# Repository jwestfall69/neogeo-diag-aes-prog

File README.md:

# neogeo-diag-aes-prog

## Overview
This is a custom NeoGeo AES Prog board that is used in conjunction with the [NeoGeo Diag Bios](https://github.com/jwestfall69/neogeo-diag-bios) that allows for testing the P ROM address and data buses between the motherboard and the cart slot.  Its meant to help trouble shoot getting a blue screen or if your game cart boots then crashes after a while (possible faulty P ROM bank switching).

It works by using an SRAM chip instead of a ROM for the program rom on the PROG board.  Doing this allows the diag bios to run tests on it similar to that of work ram to find issues.

Its not possible to test all lines related to the program rom, so there are 2 leds at the top of the board.  These 2 LEDs (ROMOE, PORTADDR) should be lit up when the P ROM Bus tests are running in the diag bios.

## PCB Manufacturing
PCB should be 1.6mm thickness.  With these boards likely being inserted and removed numerous times its suggested you use ENIG surface finishing and gold fingers w/45 degree chamfering.

I've been using [jlcpcb](https://jlcpcb.com/) for PCB manufacturing.  Just watch out that by default they will add an order number to the silk screen unless you tell them not to.

## BOM
| Quantity | Description | Part Number | Digikey | Notes |
|:--------:|:------------|-------------|---------|-------|
| 1        | SRAM 8Mbit 44 pin TSOP II | AS6C8016-55ZIN | [1450-1041-ND](https://www.digikey.com/en/products/detail/alliance-memory-inc/AS6C8016-55ZIN/4234600) | |
| 1        | 74LS04 pin 14 SOIC | SN74LS04DR | [296-14875-2-ND](https://www.digikey.com/en/products/detail/texas-instruments/SN74LS04DR/562927) | |
| 1        | 74LS08 pin 14 SOIC | SN74LS08DR | [296-14879-2-ND](https://www.digikey.com/en/products/detail/texas-instruments/SN74LS08DR/562906) | |
| 1        | 74LS11 pin 14 SOIC | SN74LS11DR | [296-28984-2-ND](https://www.digikey.com/en/products/detail/texas-instruments/SN74LS11DR/1571760) | |
| 5        | 100nf / 0.1uf Ceramic Capacitor 0805 Size | CL21B104KBCNNNC | [1276-1003-2-ND](https://www.digikey.com/en/products/detail/samsung-electro-mechanics/CL21B104KBCNNNC/3886661) | Any 100nf 0805 is fine |
| 2        | 1K Ohm resistor 0805 Size | ERJ-6GEYJ102V | [P1.0KACT-ND](https://www.digikey.com/en/products/detail/panasonic-electronic-components/ERJ-6GEYJ102V/83014) | Any 1K 0805 resistor is fine |
| 2        | Green LED 0805 12mcd | LTST-C171GKT | [160-1423-2-ND](https://www.digikey.com/en/products/detail/liteon/LTST-C171GKT/386793) | Other 0805 size LEDs should be fine |

## Assembly
The SRAM has a really fine pin pitch, so take your time.  Other then that nothing special.

## Usage
The prog board should be used along with a valid CHA board.  Ideally you probably want a full diag cart where the CHA board has the M1 diag rom and this PROG board.  The cart should be inserted into the slot and then boot the board with the diag bios. Goto the main menu screen.

Pick: ```P ROM BUS TESTS (CUSTOM CART)```

Since this is an AES you won't be able to change the slot number, so either press A+C to start the tests or D to go back to the main menu.

The tests will run continually until D is pressed or an issue is detected.  While the tests are running you should expect the 2 LEDs on the PROG board to be lit up.

If you attempt to run the P rom bus tests without the diag PROG board you will get a ```P2 UNWRITABLE (LOWER)``` error.

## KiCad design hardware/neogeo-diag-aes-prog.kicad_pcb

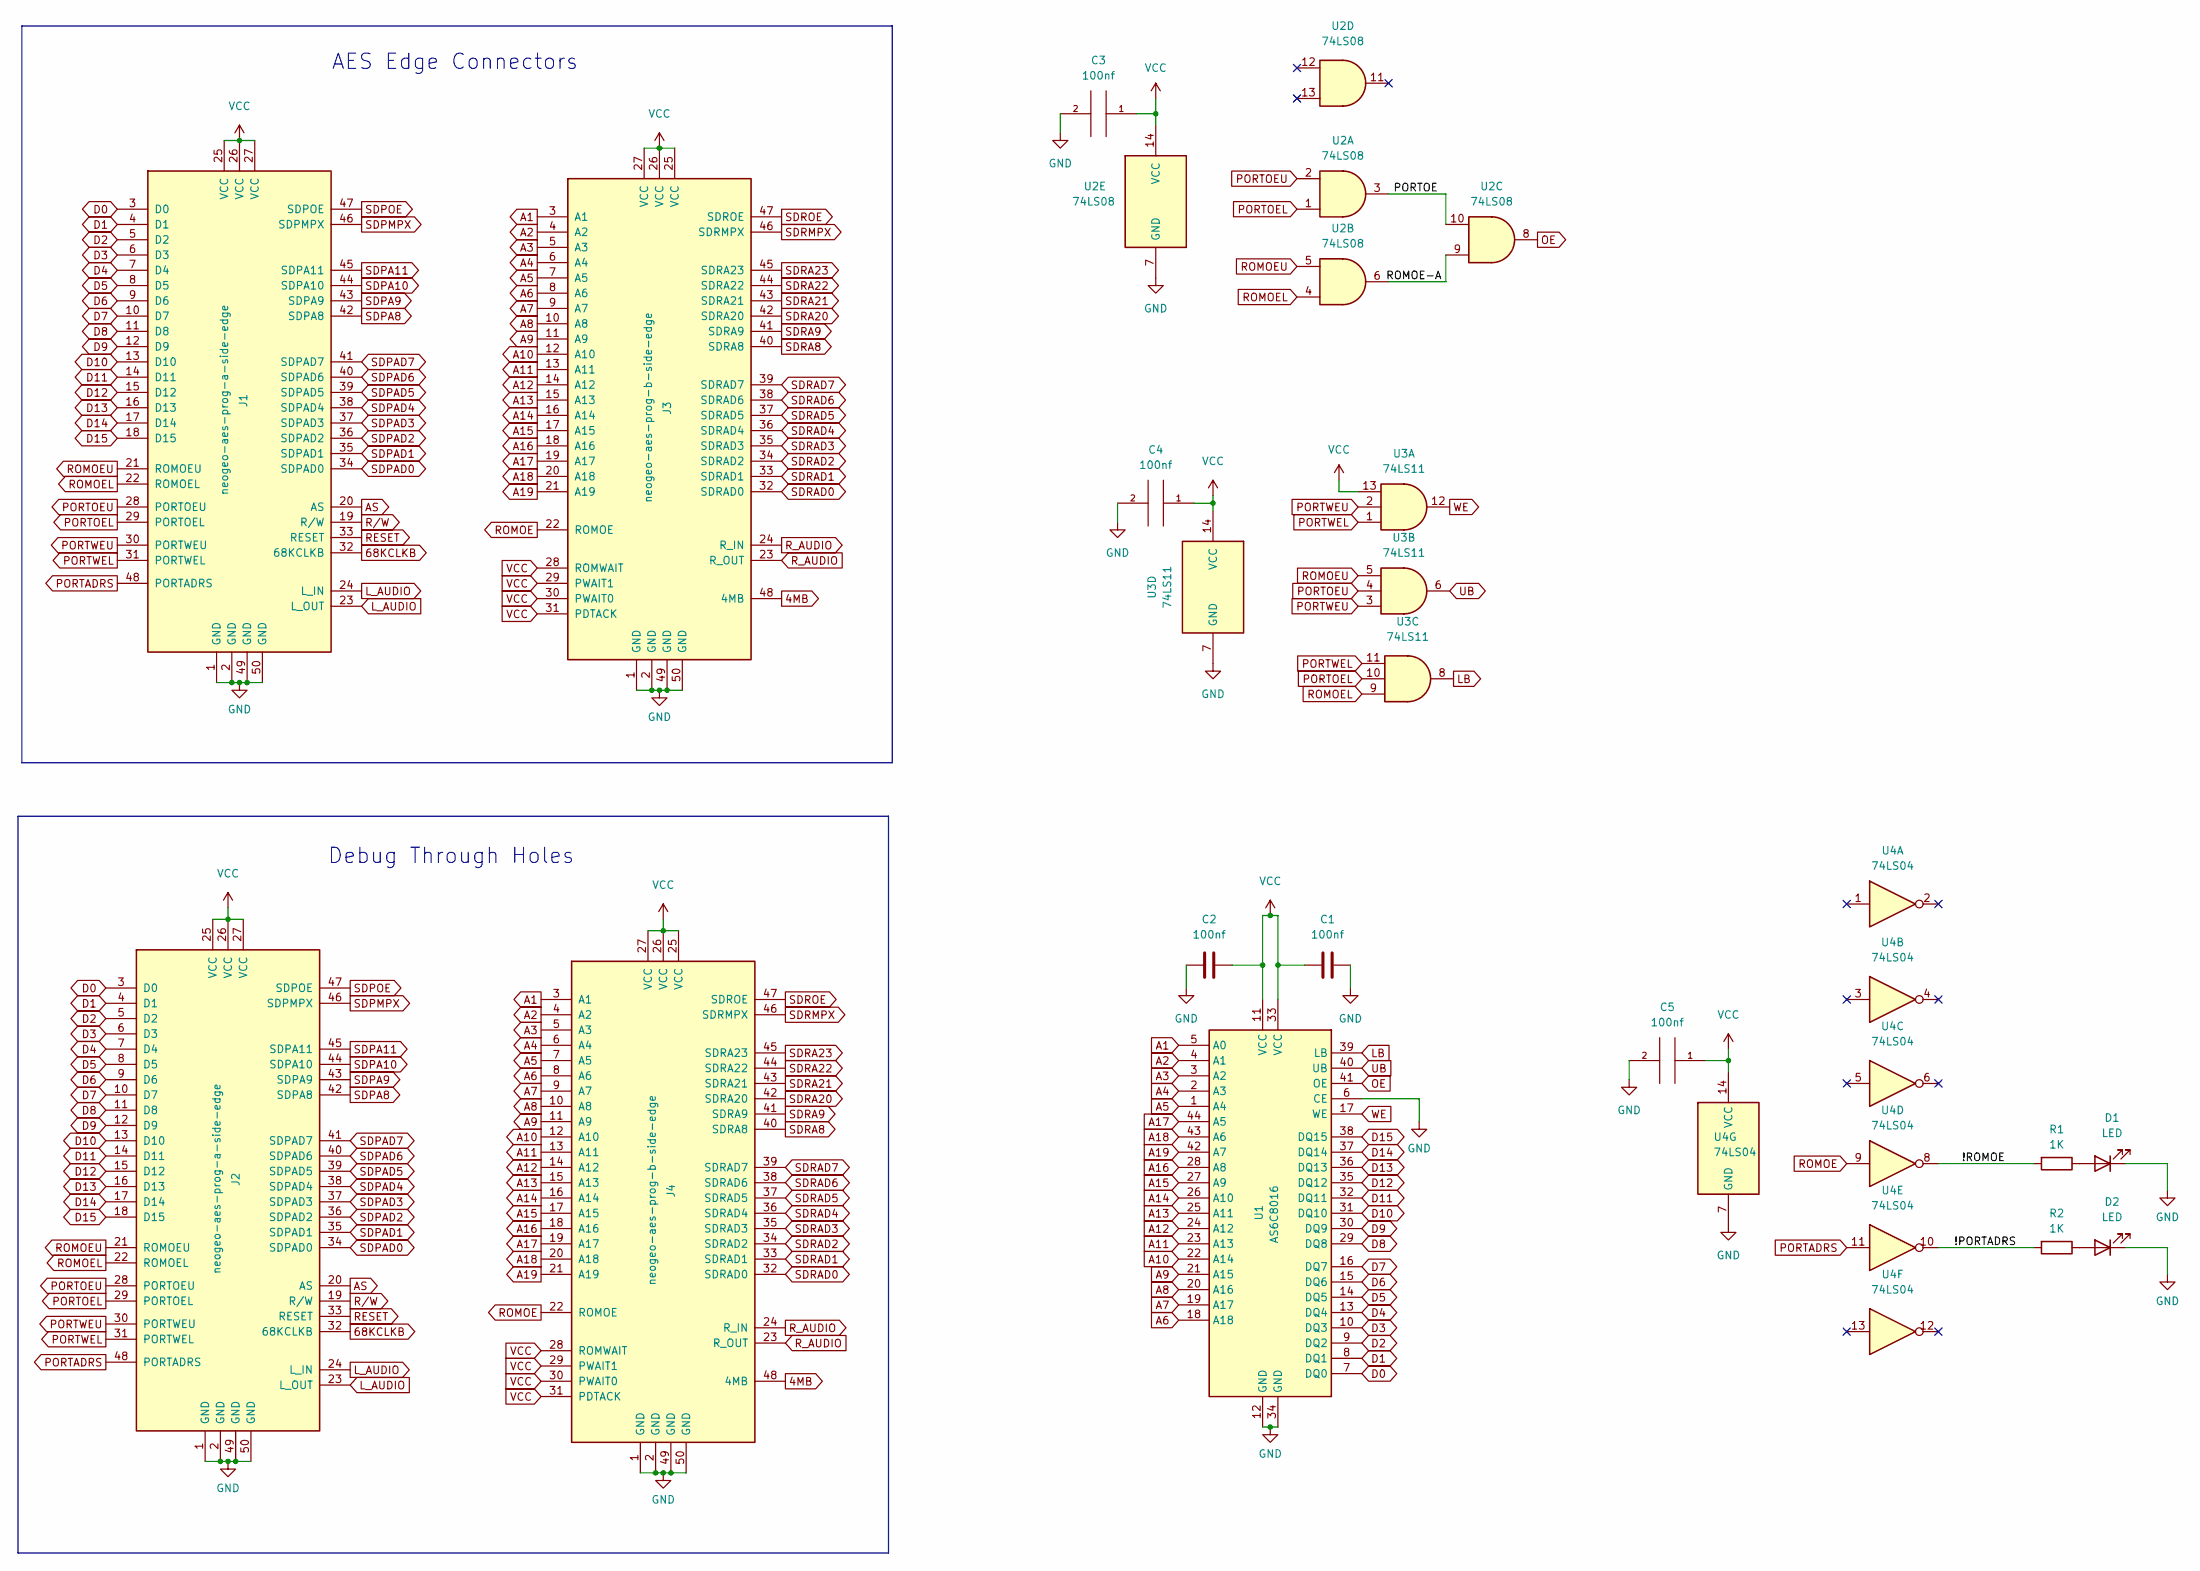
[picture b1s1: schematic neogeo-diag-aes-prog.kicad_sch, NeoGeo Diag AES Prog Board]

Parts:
C1, C2, C3, C4, C5: 100nf; C_0805_2012Metric
D1, D2: LED; LED_0805_2012Metric
J1: neogeo-aes-prog-a-side-edge
J2: neogeo-aes-prog-a-side-edge; neogeo-aes-prog-edge-test-points
J3: neogeo-aes-prog-b-side-edge
J4: neogeo-aes-prog-b-side-edge; neogeo-aes-prog-edge-test-points
R1, R2: 1K; R_0805_2012Metric
U1: AS6C8016; TSOP-II-44_10.16x18.41mm_P0.8mm
U2: 74LS08; SO-14_3.9x8.65mm_P1.27mm
U3: 74LS11; SO-14_3.9x8.65mm_P1.27mm
U4: 74LS04; SO-14_3.9x8.65mm_P1.27mm

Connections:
4MB: J3.48 (4MB), J4.48 (4MB)
68KCLKB: J1.32 (68KCLKB), J2.32 (68KCLKB)
/!PORTADRS: R2.2, U4.10
/!ROMOE: R1.2, U4.8
/PORTOE: U2.3, U2.10
/ROMOE-A: U2.6, U2.9
A1: J3.3 (A1), J4.3 (A1), U1.5 (A0)
A2: J3.4 (A2), J4.4 (A2), U1.4 (A1)
A3: J3.5 (A3), J4.5 (A3), U1.3 (A2)
A4: J3.6 (A4), J4.6 (A4), U1.2 (A3)
A5: J3.7 (A5), J4.7 (A5), U1.1 (A4)
A6: J3.8 (A6), J4.8 (A6), U1.18 (A18)
A7: J3.9 (A7), J4.9 (A7), U1.19 (A17)
A8: J3.10 (A8), J4.10 (A8), U1.20 (A16)
A9: J3.11 (A9), J4.11 (A9), U1.21 (A15)
A10: J3.12 (A10), J4.12 (A10), U1.22 (A14)
A11: J3.13 (A11), J4.13 (A11), U1.23 (A13)
A12: J3.14 (A12), J4.14 (A12), U1.24 (A12)
A13: J3.15 (A13), J4.15 (A13), U1.25 (A11)
A14: J3.16 (A14), J4.16 (A14), U1.26 (A10)
A15: J3.17 (A15), J4.17 (A15), U1.27 (A9)
A16: J3.18 (A16), J4.18 (A16), U1.28 (A8)
A17: J3.19 (A17), J4.19 (A17), U1.44 (A5)
A18: J3.20 (A18), J4.20 (A18), U1.43 (A6)
A19: J3.21 (A19), J4.21 (A19), U1.42 (A7)
AS: J1.20 (AS), J2.20 (AS)
D0: J1.3 (D0), J2.3 (D0), U1.7 (DQ0)
D1: J1.4 (D1), J2.4 (D1), U1.8 (DQ1)
D2: J1.5 (D2), J2.5 (D2), U1.9 (DQ2)
D3: J1.6 (D3), J2.6 (D3), U1.10 (DQ3)
D4: J1.7 (D4), J2.7 (D4), U1.13 (DQ4)
D5: J1.8 (D5), J2.8 (D5), U1.14 (DQ5)
D6: J1.9 (D6), J2.9 (D6), U1.15 (DQ6)
D7: J1.10 (D7), J2.10 (D7), U1.16 (DQ7)
D8: J1.11 (D8), J2.11 (D8), U1.29 (DQ8)
D9: J1.12 (D9), J2.12 (D9), U1.30 (DQ9)
D10: J1.13 (D10), J2.13 (D10), U1.31 (DQ10)
D11: J1.14 (D11), J2.14 (D11), U1.32 (DQ11)
D12: J1.15 (D12), J2.15 (D12), U1.35 (DQ12)
D13: J1.16 (D13), J2.16 (D13), U1.36 (DQ13)
D14: J1.17 (D14), J2.17 (D14), U1.37 (DQ14)
D15: J1.18 (D15), J2.18 (D15), U1.38 (DQ15)
GND: C1.1, C2.2, C3.2, C4.2, C5.2, D1.1 (K), D2.1 (K), J1.1 (GND), J1.2 (GND), J1.49 (GND), J1.50 (GND), J2.1 (GND), J2.2 (GND), J2.49 (GND), J2.50 (GND), J3.1 (GND), J3.2 (GND), J3.49 (GND), J3.50 (GND), J4.1 (GND), J4.2 (GND), J4.49 (GND), J4.50 (GND), U1.6 (CE), U1.12 (GND), U1.34 (GND), U2.7 (GND), U3.7 (GND), U4.7 (GND)
LB: U1.39 (LB), U3.8
L_AUDIO: J1.23 (L_OUT), J1.24 (L_IN), J2.23 (L_OUT), J2.24 (L_IN)
unnamed: D1.2 (A), R1.1
unnamed: D2.2 (A), R2.1
OE: U1.41 (OE), U2.8
PORTADRS: J1.48 (PORTADRS), J2.48 (PORTADRS), U4.11
PORTOEL: J1.29 (PORTOEL), J2.29 (PORTOEL), U2.1, U3.10
PORTOEU: J1.28 (PORTOEU), J2.28 (PORTOEU), U2.2, U3.4
PORTWEL: J1.31 (PORTWEL), J2.31 (PORTWEL), U3.1, U3.11
PORTWEU: J1.30 (PORTWEU), J2.30 (PORTWEU), U3.2, U3.3
RESET: J1.33 (RESET), J2.33 (RESET)
ROMOE: J3.22 (ROMOE), J4.22 (ROMOE), U4.9
ROMOEL: J1.22 (ROMOEL), J2.22 (ROMOEL), U2.4, U3.9
ROMOEU: J1.21 (ROMOEU), J2.21 (ROMOEU), U2.5, U3.5
R_AUDIO: J3.23 (R_OUT), J3.24 (R_IN), J4.23 (R_OUT), J4.24 (R_IN)
R/W: J1.19 (R/W), J2.19 (R/W)
SDPA8: J1.42 (SDPA8), J2.42 (SDPA8)
SDPA9: J1.43 (SDPA9), J2.43 (SDPA9)
SDPA10: J1.44 (SDPA10), J2.44 (SDPA10)
SDPA11: J1.45 (SDPA11), J2.45 (SDPA11)
SDPAD0: J1.34 (SDPAD0), J2.34 (SDPAD0)
SDPAD1: J1.35 (SDPAD1), J2.35 (SDPAD1)
SDPAD2: J1.36 (SDPAD2), J2.36 (SDPAD2)
SDPAD3: J1.37 (SDPAD3), J2.37 (SDPAD3)
SDPAD4: J1.38 (SDPAD4), J2.38 (SDPAD4)
SDPAD5: J1.39 (SDPAD5), J2.39 (SDPAD5)
SDPAD6: J1.40 (SDPAD6), J2.40 (SDPAD6)
SDPAD7: J1.41 (SDPAD7), J2.41 (SDPAD7)
SDPMPX: J1.46 (SDPMPX), J2.46 (SDPMPX)
SDPOE: J1.47 (SDPOE), J2.47 (SDPOE)
SDRA8: J3.40 (SDRA8), J4.40 (SDRA8)
SDRA9: J3.41 (SDRA9), J4.41 (SDRA9)
SDRA20: J3.42 (SDRA20), J4.42 (SDRA20)
SDRA21: J3.43 (SDRA21), J4.43 (SDRA21)
SDRA22: J3.44 (SDRA22), J4.44 (SDRA22)
SDRA23: J3.45 (SDRA23), J4.45 (SDRA23)
SDRAD0: J3.32 (SDRAD0), J4.32 (SDRAD0)
SDRAD1: J3.33 (SDRAD1), J4.33 (SDRAD1)
SDRAD2: J3.34 (SDRAD2), J4.34 (SDRAD2)
SDRAD3: J3.35 (SDRAD3), J4.35 (SDRAD3)
SDRAD4: J3.36 (SDRAD4), J4.36 (SDRAD4)
SDRAD5: J3.37 (SDRAD5), J4.37 (SDRAD5)
SDRAD6: J3.38 (SDRAD6), J4.38 (SDRAD6)
SDRAD7: J3.39 (SDRAD7), J4.39 (SDRAD7)
SDRMPX: J3.46 (SDRMPX), J4.46 (SDRMPX)
SDROE: J3.47 (SDROE), J4.47 (SDROE)
UB: U1.40 (UB), U3.6
VCC: C1.2, C2.1, C3.1, C4.1, C5.1, J1.25 (VCC), J1.26 (VCC), J1.27 (VCC), J2.25 (VCC), J2.26 (VCC), J2.27 (VCC), J3.25 (VCC), J3.26 (VCC), J3.27 (VCC), J3.28 (ROMWAIT), J3.29 (PWAIT1), J3.30 (PWAIT0), J3.31 (PDTACK), J4.25 (VCC), J4.26 (VCC), J4.27 (VCC), J4.28 (ROMWAIT), J4.29 (PWAIT1), J4.30 (PWAIT0), J4.31 (PDTACK), U1.11 (VCC), U1.33 (VCC), U2.14 (VCC), U3.13, U3.14 (VCC), U4.14 (VCC)
WE: U1.17 (WE), U3.12

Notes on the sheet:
Debug Through Holes
AES Edge Connectors

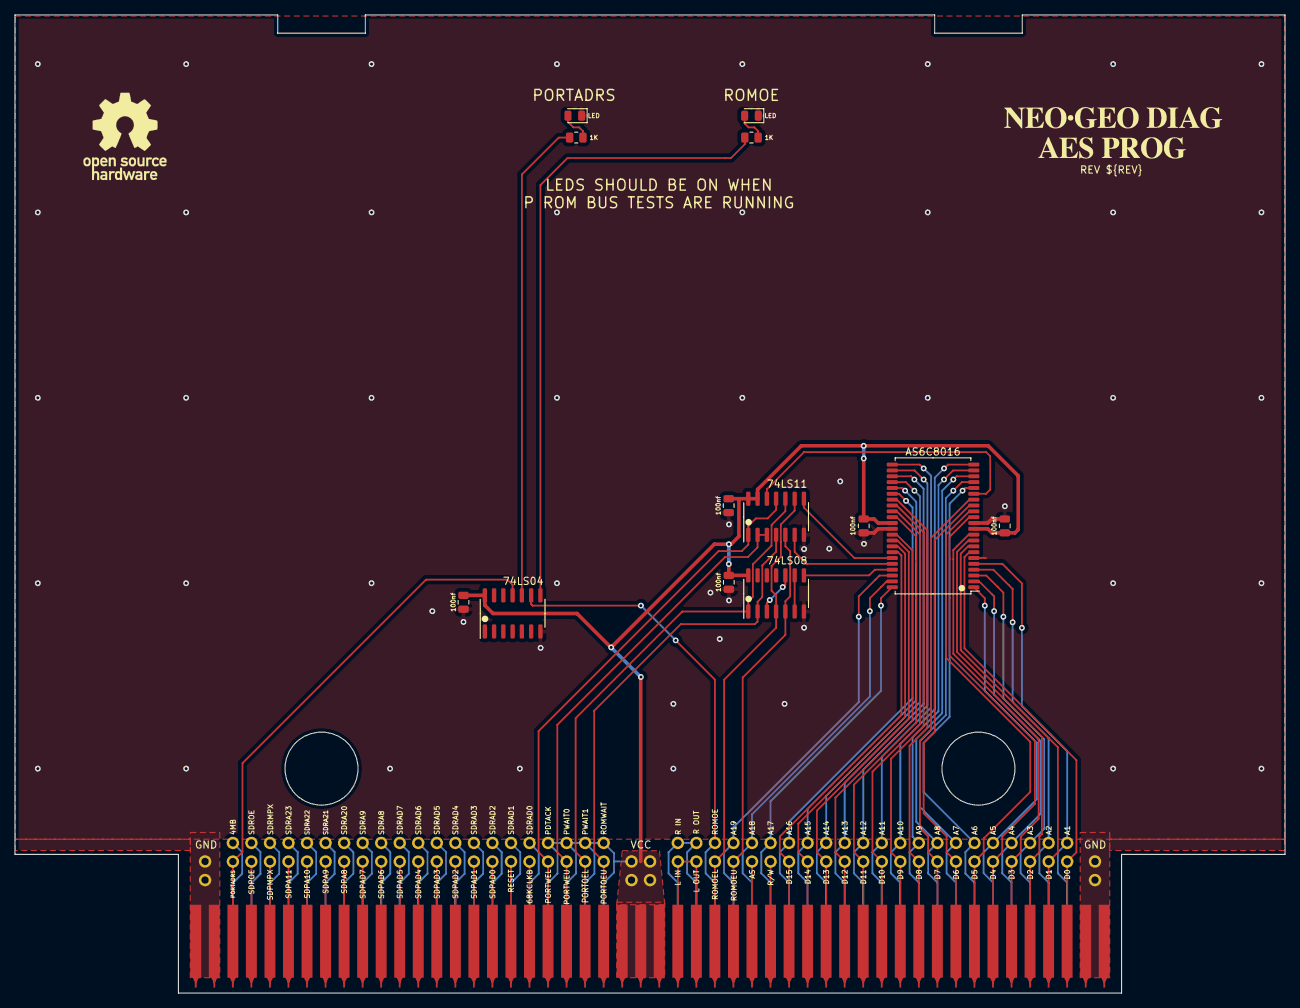
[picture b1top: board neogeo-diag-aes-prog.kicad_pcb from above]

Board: 2 copper layers, 174.0 x 134.0 mm, 17 parts (1 on the bottom side), 92 nets.

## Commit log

2023-02-26 Skeleton
2023-02-26 Pull updated kicad library
2023-03-07 Bump neogeo-diag kicard library to newest version
2023-03-07 Add license
2023-03-07 Initial schematic/pcb
2023-03-07 Fix silkscreen typo 68KCLB -> 68KCLKB
2023-03-11 Pull in newer neogeo-diag-kicad-library
2023-03-11 Add logo
2023-03-11 Set output dir
2023-03-25 Docs
